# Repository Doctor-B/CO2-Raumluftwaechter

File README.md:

# CO2-Raumluftwaechter
Der CO2-Raumluftwächter misst mit Hilfe des SCD30 von Sensirion den CO2-Gehalt der Raumluft und setzt optisch die CO2-Konzentration um, so dass Klassenräumen bedarfsgerechter gelüftet werden können. Optional kann der CO2-Raumluftwächter mit einer Echtzeituhr DS3231 (Batteriegepuffert) und SD-Card-Slot und/oder OLED-Display ausgestattet werden. Per Arduino Nano V3.0 werden die Messwerte vom SCD30 abgerufen und können auf SD-Card protokolliert, wie auch in Echtzeit auf einem OLED-Display ausgegeben werden.

# Hardware Bestandteile
* Trägerplatine
* Arduino nano V3 _[THT]_
* SCD30 _[THT]_
* WS2812b LED Ring mit 16 LEDs als Anzeige mit 100nF Abblockondensatoren _[SMD]_
* Levelshifter BSS138BKSH _[SMD]_
* (optional) Echtzeituhr DS3231 mit Batteriepufferung CR1220 _[SMD]_
* (optional) I2C OLED Display 128 x 64 (VCC GND auf Pin 1 und 2 vertauschbar per Lötbrücke) _[THT]_
* (optional) SD-Card Slot _[SMD]_

# Aufbau mit interaktiven BOM
Mit Hilfe der [interaktiven BOM](https://htmlpreview.github.io/?https://github.com/Doctor-B/CO2-Raumluftwaechter/blob/main/PCB/KiCAD_RaumluftWaechter_V1.00_CC_BY-NC-SA_4.0/bom/ibom.html) ist es einfach, einen Überblick über die Bauteile und das Bestücken des Raumluftwächters zu behalten.

# License 

The contents of this repository is released under the following license:

- the "Creative Commons Attribution-NonCommercial-ShareAlike 4.0 International License" (CC BY-NC-SA 4.0) full text of this license is included in the [LICENSE.CC_NC-BY-SA-4.0](https://github.com/Doctor-B/CO2-Raumluftwaechter/blob/main/LICENSE.CC_BY-NC-SA) file and a copy can also be found at https://creativecommons.org/licenses/by-nc-sa/4.0/

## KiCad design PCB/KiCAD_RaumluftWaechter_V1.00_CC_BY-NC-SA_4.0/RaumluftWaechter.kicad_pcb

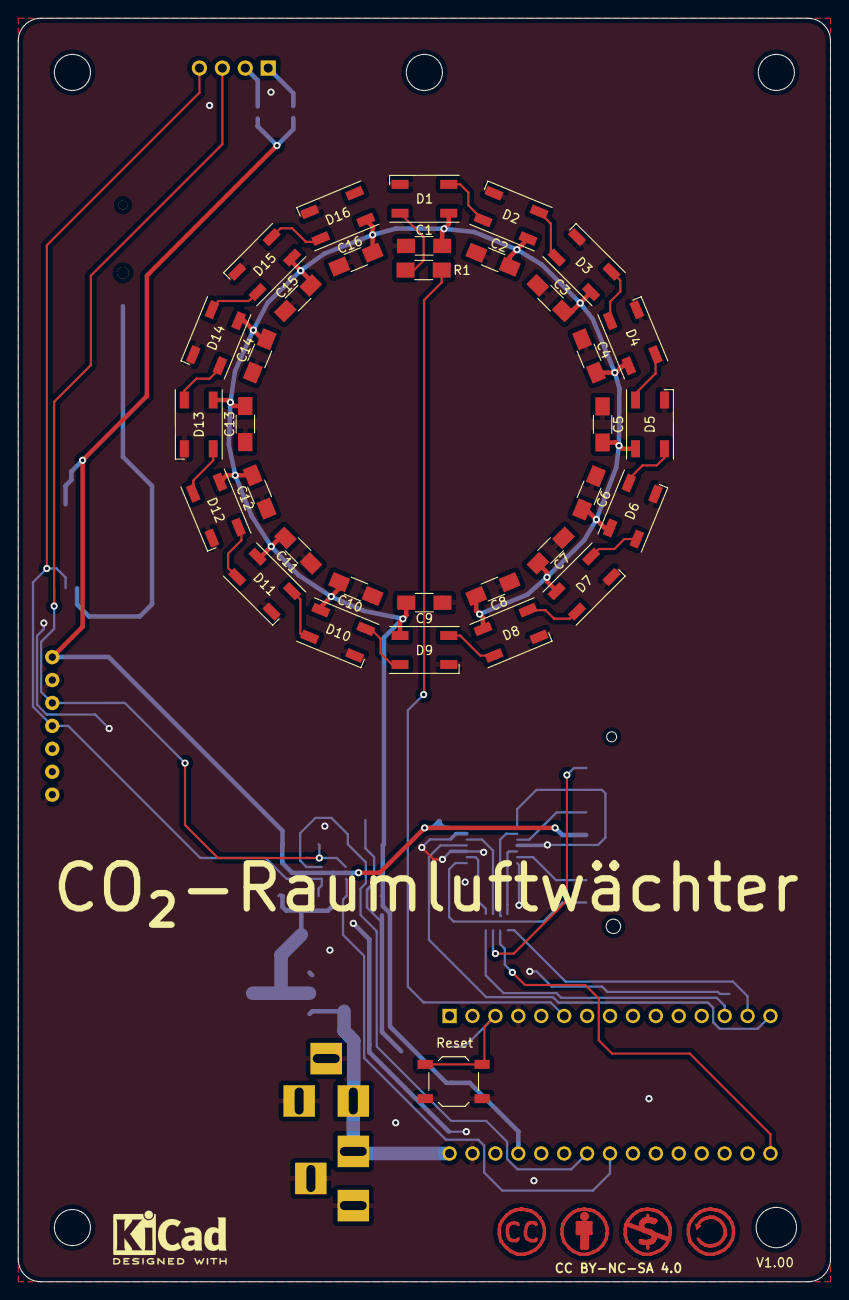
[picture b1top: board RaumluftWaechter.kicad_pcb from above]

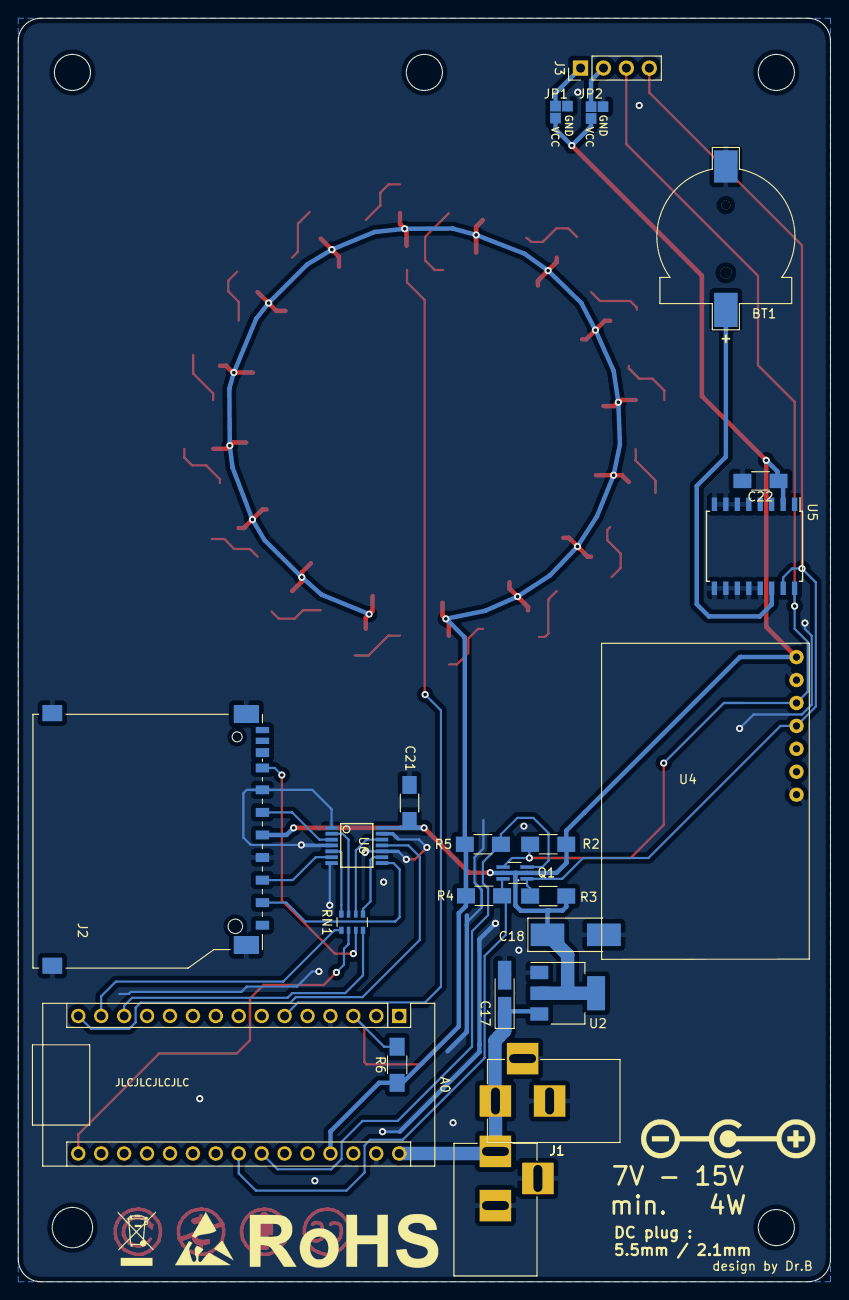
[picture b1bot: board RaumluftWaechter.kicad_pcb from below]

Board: 2 copper layers, 90.0 x 140.0 mm, 57 parts (23 on the bottom side), 40 nets.

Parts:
A0: Arduino_Nano_v3.x; Arduino_Nano
BT1: Battery_Cell; CR1220_mod
C1, C2, C3, C4, C5, C6, C7, C8, C9, C10, C11, C12, C13, C14, C15, C16, C21, C22: 100n; C_1206_HandSoldering
C17: 10µF; CP_Tantalum_Case-A_EIA-3216-18_Hand
C18: 100µF; CP_Tantalum_Case-C_EIA-6032-28_Hand
D1, D2, D3, D4, D5, D6, D7, D8, D9, D10, D11, D12, D13, D14, D15, D16: WS2812B; LED_WS2812B-PLCC4_Handsoldering
J1, J1#2: Barrel_Jack_Switch; BARREL_JACK
J2: SD_Card_mod; SD_Card_mod_hand_solder
J3: Conn_01x04_Female; Pin_Header_Straight_1x04_Pitch2.54mm
JP1, JP2: Jumper_3_Open; Solder-Jumper-3_Pads_mirror_L
Q1: BSS138BKS; SOT-363_SC-70-6_Handsoldering
R1: 330R; R_1206_HandSoldering
R2, R3, R4, R5: 2K; R_1206_HandSoldering
R6: 6.8k - 10k; R_1206_HandSoldering
RN1: 3.3k; R_Array_Convex_4x0603
SW1: SW_Push; SW_SPST_TL3342
U2: LM1117-3.3; SOT-223
U4: SCD30
U5: DS3231M; SOIC-16W_7.5x10.3mm_Pitch1.27mm
U6: 74LVC125; SSOP-14

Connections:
/CS: A0.13, RN1.4
/GND: A0.4, A0.29, BT1.2, C1.1, C2.1, C3.1, C4.1, C5.1, C6.1, C7.1, C8.1, C9.1, C10.1, C11.1, C12.1, C13.1, C14.1, C15.1, C16.1, C17.2, C18.2, C21.2, C22.2, D1.3, D2.3, D3.3, D4.3, D5.3, D6.3, D7.3, D8.3, D9.3, D10.3, D11.3, D12.3, D13.3, D14.3, D15.3, D16.3, J1.2, J1.3, J1#2.2, J1#2.3, J2.3, J2.6, J2.12, J2.13, J2.14, J2.15, JP1.1, JP2.1, SW1.2, U2.1, U4.2, U4.7, U5.5, U5.6, U5.7, U5.8, U5.9, U5.10, U5.11, U5.12, U5.13, U6.1, U6.4, U6.7, U6.10, U6.13
/GNDD: J3.2, JP2.2
/MISO: A0.15, U6.11
/MOSI: A0.14, RN1.1
/SCK: A0.16, RN1.2
/SCLA: A0.24, Q1.3, R5.1
/SCLB: J3.3, Q1.4, R2.1, U4.3, U5.16
/SDAA: A0.23, Q1.6, R4.1
/SDAB: J3.4, Q1.1, R3.1, U4.4, U5.15
/SDCS: J2.1, U6.8
/SDMISO: J2.7, RN1.3
/SDMOSI: J2.2, U6.6
/SDSCK: J2.5, U6.3
/VCC: A0.27, C1.2, C2.2, C3.2, C4.2, C5.2, C6.2, C7.2, C8.2, C9.2, C10.2, C11.2, C12.2, C13.2, C14.2, C15.2, C16.2, D1.1, D2.1, D3.1, D4.1, D5.1, D6.1, D7.1, D8.1, D9.1, D10.1, D11.1, D12.1, D13.1, D14.1, D15.1, D16.1, R4.2, R5.2, R6.1
/VCC12: A0.30, C17.1, J1.1, J1#2.1, U2.3
/VCC33: C18.1, C21.1, C22.1, J2.4, J3.1, JP1.2, JP1.3, JP2.3, Q1.2, Q1.5, R2.2, R3.2, U2.2, U4.1, U5.2, U6.14
/VCCB: BT1.1, U5.14
unnamed: A0.3, R6.2, SW1.1
unnamed: A0.6, R1.2
unnamed: D1.2, D2.4
unnamed: D1.4, R1.1
unnamed: D2.2, D3.4
unnamed: D3.2, D4.4
unnamed: D4.2, D5.4
unnamed: D5.2, D6.4
unnamed: D6.2, D7.4
unnamed: D7.2, D8.4
unnamed: D8.2, D9.4
unnamed: D10.2, D11.4
unnamed: D9.2, D10.4
unnamed: D11.2, D12.4
unnamed: D12.2, D13.4
unnamed: D13.2, D14.4
unnamed: D14.2, D15.4
unnamed: D15.2, D16.4
unnamed: RN1.5, U6.9
unnamed: RN1.6, U6.12
unnamed: RN1.7, U6.2
unnamed: RN1.8, U6.5

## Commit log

2021-02-04 Create LICENSE.CC_BY-NC-SA
2021-02-04 Update LICENSE.CC_BY-NC-SA
2021-02-10 Changes
    Added KiCAD files
    Added Arduino program V0.63
    Added Picture of CO2-Raumluftwaechter
2021-02-10 picture exchange
2021-02-10 added 3d model and drawing
2021-02-10 added drawing and 3d model holder for table
2021-02-16 new Arduino version 0.64
    Added: Arduino version and correction value of meassuered CO2 level will be shown with the 16 LEDs, when the Arduino is powerd on
2021-03-13 new Arduino Firmware 0.65
    During start process of the Arduino, the 16 LEDs are used for displaying some useful information. Each single step has a duration time of two seconds.
    1st they are performing a self-test (all LEDs war showing white)
    2nd they are showing the device number (LED1 = bit 0, LED2 = bit 1, etc.)
    3rd they show firmware version and correction value for CO2 level reading.
    LED1 is showing main version number with the colours blue = 0, yellow = 1, violet = 2 and cyan blue = 3, black is unknown;
    LED2-7 are showing subversion number as binary: LED2 = bit 0, LED3 = bit 1, etc.;
2021-03-19 interactive BOM
2021-04-23 minor update of schematic, PCB and ibom
2021-06-13 Update README.md
    Link zur interaktiven BOM eingefügt.

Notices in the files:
README.md:
License ![CC BY-NC-SA 4.0 Logo](/Bilder/CC_BY-NC-SA.png):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
